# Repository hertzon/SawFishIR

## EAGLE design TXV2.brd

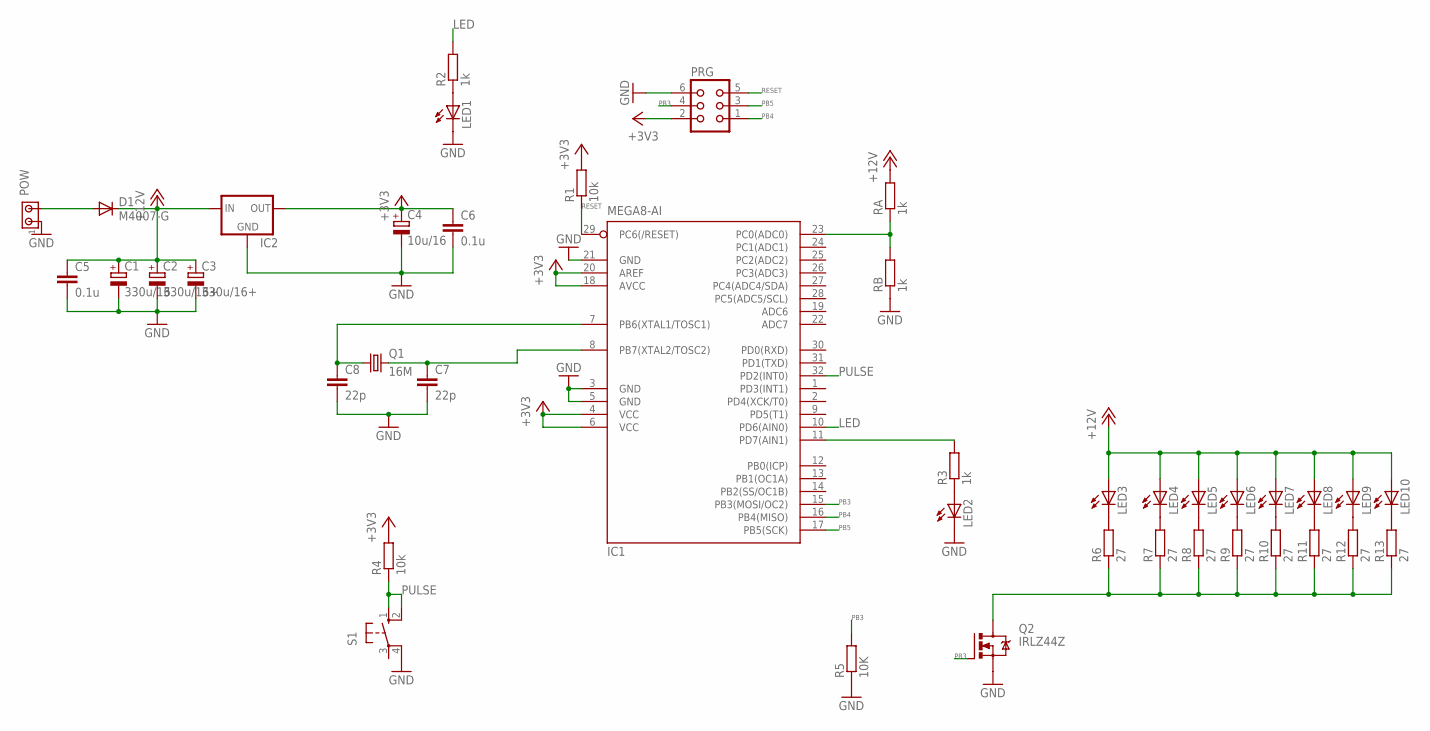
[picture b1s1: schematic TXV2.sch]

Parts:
C1: 330u/16; E2,5-7
C2, C3: 330u/16+; E2,5-7
C4: 10u/16; E2,5-6
C5, C6: 0.1u; C0402
C7, C8: 22p; C0805
D1: M4007-G; SOD-123_MINI-SMA
IC1: MEGA8-AI; TQFP32-08
IC2: 78LXX
LED1, LED2, LED3, LED4, LED5, LED6, LED7, LED8, LED9, LED10: LED5MM
POW: MTA02-100; 10X02MTA
PRG: CON06
Q1: 16M; HC49UP
Q2: IRLZ44Z; TO220BH
R1, R4: 10k; M1206
R2, R3: 1k; M1206
R5: 10K; M1206
R6, R7, R8, R9, R10, R11, R12, R13: 27; 0204/7
RA: 1k; M1206
RB: 1k; M1206
S1: 10-XX; B3F-10XX

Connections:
+3V3: C4.+, C6.1, IC1.4 (VCC), IC1.6 (VCC), IC1.18 (AVCC), IC1.20 (AREF), IC2.OUT, PRG.2, R1.2, R4.2
+12V: C1.+, C2.+, C3.+, C5.1, D1.C, IC2.IN, LED3.A, LED4.A, LED5.A, LED6.A, LED7.A, LED8.A, LED9.A, LED10.A, RA.2
GND: C1.-, C2.-, C3.-, C4.-, C5.2, C6.2, C7.2, C8.2, IC1.3 (GND), IC1.5 (GND), IC1.21 (GND), IC2.GND, LED1.K (C), LED2.K (C), POW.1, PRG.6, Q2.S, R5.1, RB.1, S1.4 (P1)
LED: IC1.10 (PD6(AIN0)), R2.2
unnamed: LED3.K (C), R6.2
unnamed: LED1.A, R2.1
unnamed: IC1.11 (PD7(AIN1)), R3.2
unnamed: LED2.A, R3.1
unnamed: LED4.K (C), R7.2
unnamed: C8.1, IC1.7 (PB6(XTAL1/TOSC1)), Q1.1
unnamed: C7.1, IC1.8 (PB7(XTAL2/TOSC2)), Q1.2
unnamed: LED5.K (C), R8.2
unnamed: LED6.K (C), R9.2
unnamed: LED7.K (C), R10.2
unnamed: LED8.K (C), R11.2
unnamed: LED9.K (C), R12.2
unnamed: LED10.K (C), R13.2
unnamed: IC1.23 (PC0(ADC0)), RA.1, RB.2
unnamed: Q2.D, R6.1, R7.1, R8.1, R9.1, R10.1, R11.1, R12.1, R13.1
unnamed: D1.A, POW.2
PB3: IC1.15 (PB3(MOSI/OC2)), PRG.4, Q2.G, R5.2
PB4: IC1.16 (PB4(MISO)), PRG.1
PB5: IC1.17 (PB5(SCK)), PRG.3
PULSE: IC1.32 (PD2(INT0)), R4.1, S1.1 (S), S1.2 (S1)
RESET: IC1.29 (PC6(/RESET)), PRG.5, R1.1

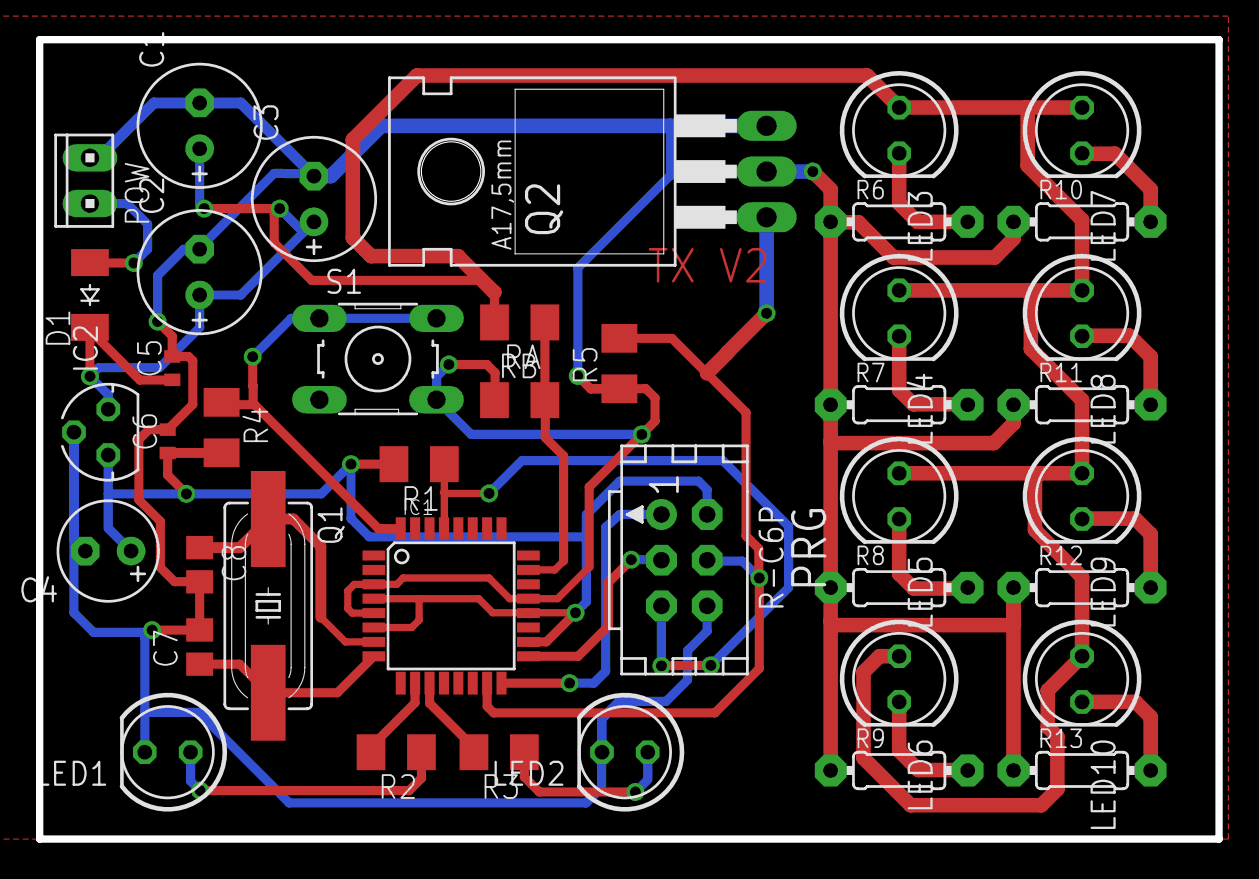
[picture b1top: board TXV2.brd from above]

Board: 2 copper layers, 65.5 x 44.4 mm, 41 parts (0 on the bottom side), 25 nets.

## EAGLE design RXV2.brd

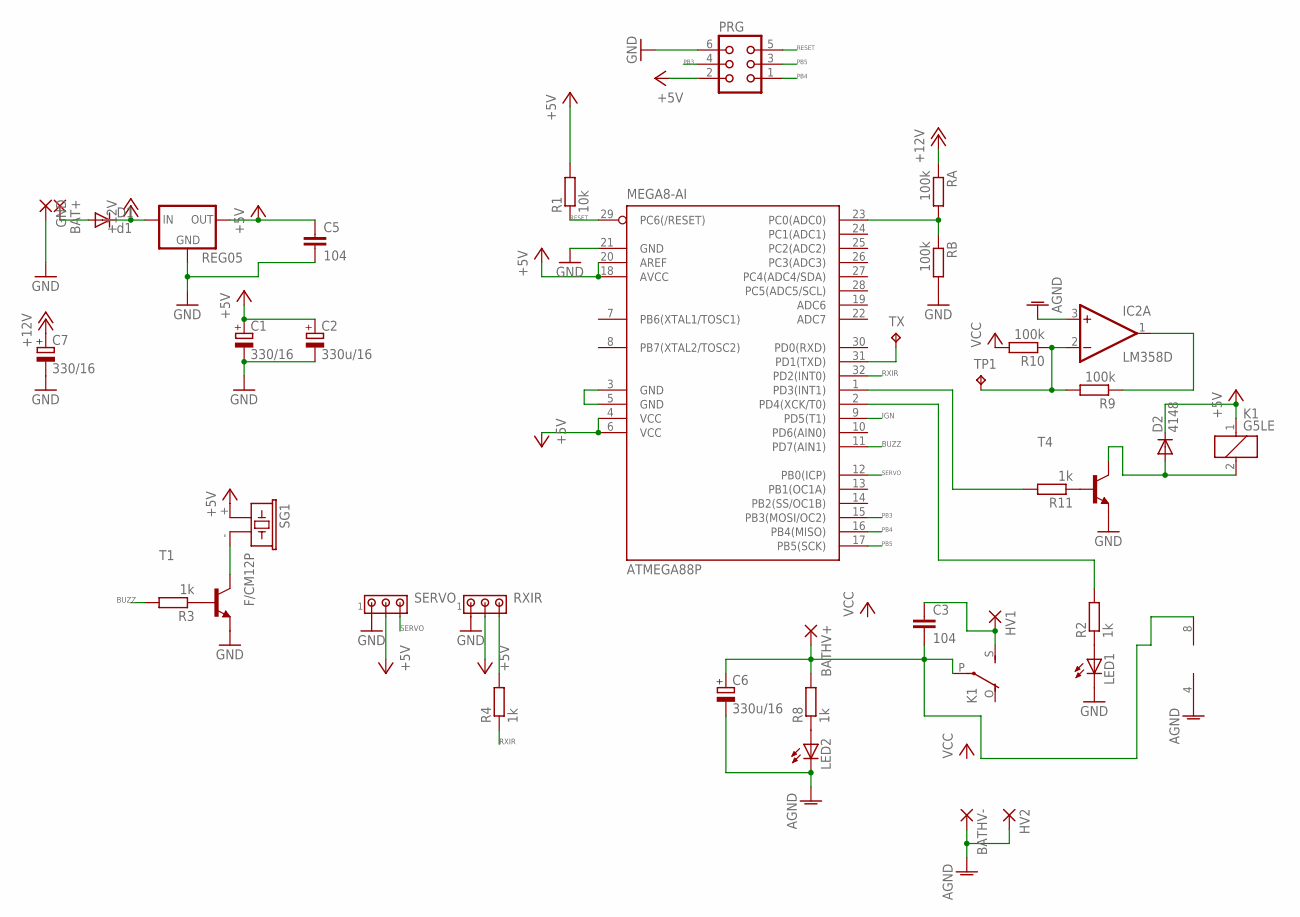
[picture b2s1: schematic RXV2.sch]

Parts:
ATMEGA88P: MEGA8-AI; TQFP32-08
BAT+: SMD5; SMD2,54-5,08
BATHV+: SMD5; SMD2,54-5,08
BATHV-: SMD5; SMD2,54-5,08
C1, C7: 330/16; E2,5-7
C2, C6: 330u/16; E2,5-6
C3: 104; C0805
C5: 104; C2.5-2
D1: d1; SOD-123_MINI-SMA
D2: 4148; DO35-7
GND: SMD5; SMD2,54-5,08
HV1, HV2: SMD5; SMD2,54-5,08
IC2: LM358D; SO08
K1: G5LE
LED1, LED2: LEDCHIPLED_0805; CHIPLED_0805
PRG: CON06
R1: 10k; M1206
R2, R3, R4, R8, R11: 1k; M1206
R9, R10: 100k; M1206
RA: 100k; M1206
RB: 100k; M1206
REG05: 78XXS
RXIR: MTA03-100; 10X03MTA
SERVO: MTA03-100; 10X03MTA
SG1: F/CM12P
T1, T4: MMBT2222ALT1-NPN-SOT23-BEC; SOT23-BEC
TP1: TPTP19R; TP19R
TX: TPTP19R; TP19R

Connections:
+5V: ATMEGA88P.4 (VCC), ATMEGA88P.6 (VCC), ATMEGA88P.18 (AVCC), ATMEGA88P.20 (AREF), C1.+, C2.+, C5.1, D2.C, K1.1, PRG.2, R1.2, REG05.OUT, RXIR.2, SERVO.2, SG1.+ (1)
+12V: C7.+, D1.C, RA.1, REG05.IN
AGND: BATHV-.1, C6.-, HV2.1, IC2.3 (+IN), IC2.4 (V-), LED2.C
BUZZ: ATMEGA88P.11 (PD7(AIN1)), R3.2
GND: ATMEGA88P.21 (GND), C1.-, C2.-, C5.2, C7.-, GND.1, LED1.C, PRG.6, RB.2, REG05.GND, RXIR.1, SERVO.1, T1.E, T4.E
IGN: ATMEGA88P.9 (PD5(T1))
unnamed: ATMEGA88P.3 (GND), ATMEGA88P.5 (GND)
unnamed: BAT+.1, D1.A
unnamed: R11.1, T4.B
unnamed: SG1.- (2), T1.C
unnamed: LED1.A, R2.1
unnamed: R3.1, T1.B
unnamed: R4.2, RXIR.3
unnamed: BATHV+.1, C3.2, C6.+, IC2.8 (V+), K1.P, R8.2
unnamed: ATMEGA88P.31 (PD1(TXD)), TX.TP
unnamed: ATMEGA88P.23 (PC0(ADC0)), RA.2, RB.1
unnamed: ATMEGA88P.2 (PD4(XCK/T0)), R2.2
unnamed: LED2.A, R8.1
unnamed: IC2.2 (-IN), R9.2, R10.1, TP1.TP
unnamed: IC2.1 (OUT), R9.1
unnamed: ATMEGA88P.1 (PD3(INT1)), R11.2
unnamed: C3.1, HV1.1, K1.S
unnamed: D2.A, K1.2, T4.C
PB3: ATMEGA88P.15 (PB3(MOSI/OC2)), PRG.4
PB4: ATMEGA88P.16 (PB4(MISO)), PRG.1
PB5: ATMEGA88P.17 (PB5(SCK)), PRG.3
RESET: ATMEGA88P.29 (PC6(/RESET)), PRG.5, R1.1
RXIR: ATMEGA88P.32 (PD2(INT0)), R4.1
SERVO: ATMEGA88P.12 (PB0(ICP)), SERVO.3
VCC: R10.2

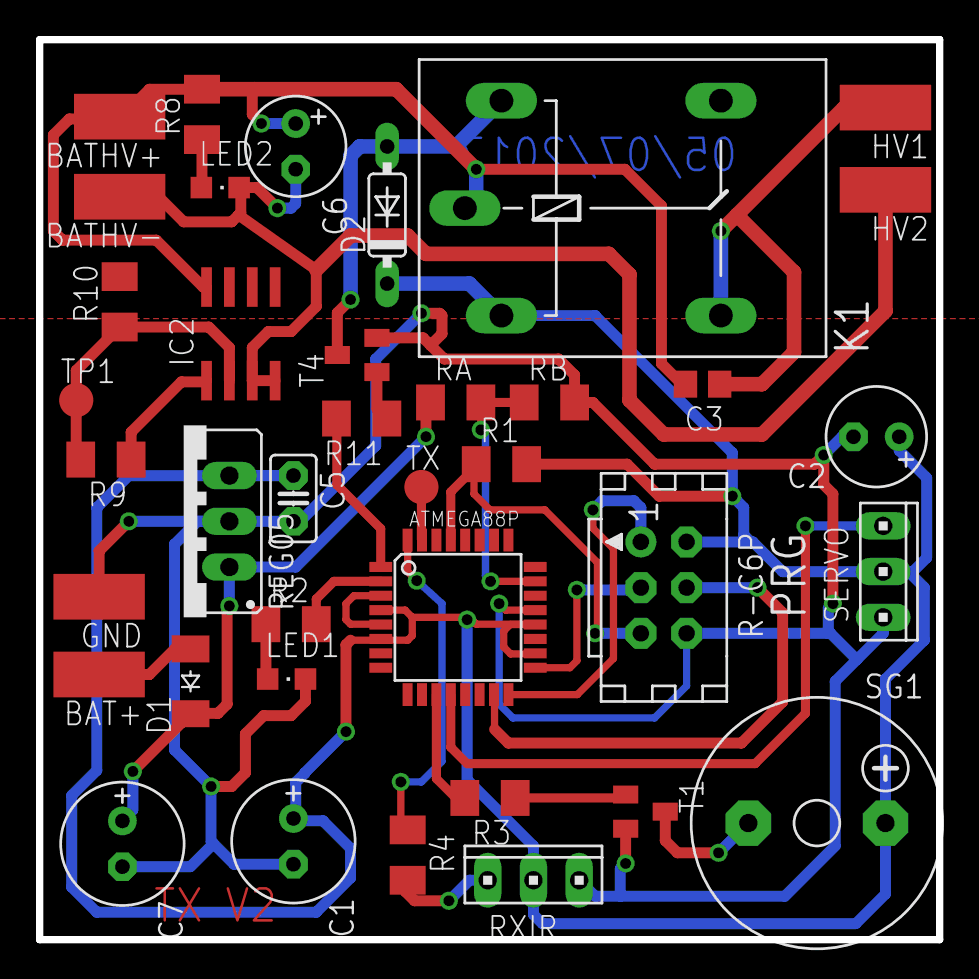
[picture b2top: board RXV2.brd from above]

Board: 2 copper layers, 50.0 x 50.0 mm, 38 parts (0 on the bottom side), 28 nets.

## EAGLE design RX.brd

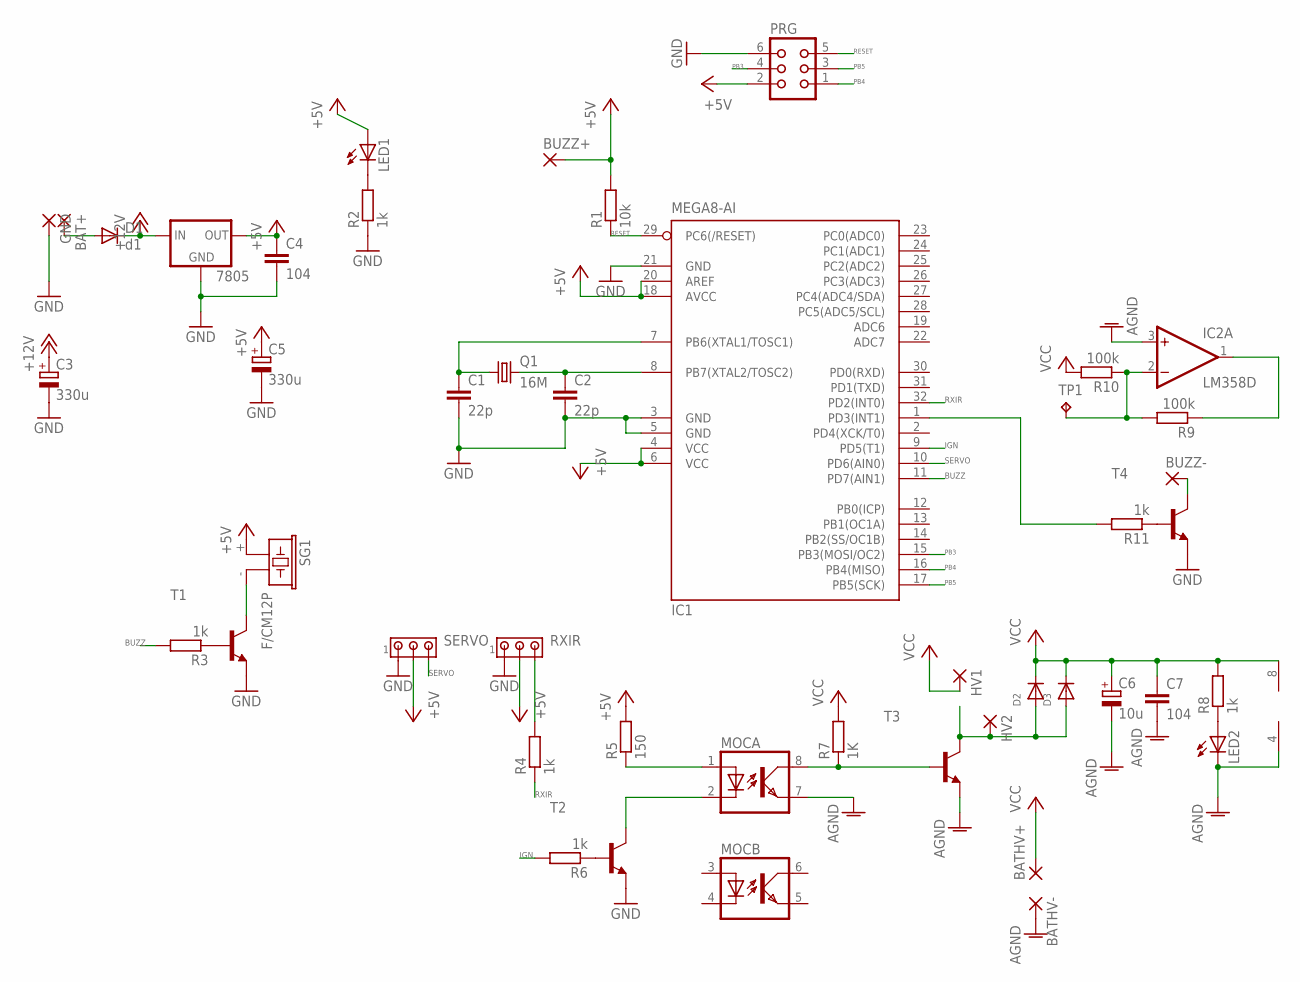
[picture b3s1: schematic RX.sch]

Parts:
7805: 78LXX
BAT+: SMD5; SMD2,54-5,08
BATHV+: SMD5; SMD2,54-5,08
BATHV-: SMD5; SMD2,54-5,08
BUZZ+: SMD2; SMD1,27-2,54
BUZZ-: SMD2; SMD1,27-2,54
C1, C2: 22p; C0805
C3, C5: 330u; 140CLH-1010
C4, C7: 104; C0805
C6: 10u; 140CLH-0810
D1: d1; SOD-123_MINI-SMA
D2, D3: DIODE_SOD-123FL; SOD-123FL
GND: SMD5; SMD2,54-5,08
HV1, HV2: SMD5; SMD2,54-5,08
IC1: MEGA8-AI; TQFP32-08
IC2: LM358D; SO08
LED1: LED3MM
LED2: LEDCHIPLED_0805; CHIPLED_0805
MOC: MOCD207M; SOIC08-FAIRCHILD
PRG: CON06
Q1: 16M; HC49UP
R1: 10k; M1206
R2, R3, R4, R6, R8, R11: 1k; M1206
R5: 150; M1206
R7: 1K; M1206
R9, R10: 100k; M1206
RXIR: MTA03-100; 10X03MTA
SERVO: MTA03-100; 10X03MTA
SG1: F/CM12P
T1, T2, T3, T4: MMBT2222ALT1-NPN-SOT23-BEC; SOT23-BEC
TP1: TPTP10R; TP10R

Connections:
+5V: 7805.OUT, BUZZ+.1, C4.1, C5.+, IC1.4 (VCC), IC1.6 (VCC), IC1.18 (AVCC), IC1.20 (AREF), LED1.A, PRG.2, R1.2, R5.2, RXIR.2, SERVO.2, SG1.+ (1)
+12V: 7805.IN, C3.+, D1.C
AGND: BATHV-.1, C6.-, C7.2, IC2.3 (+IN), IC2.4 (V-), LED2.C, MOC.7 (EMIT), T3.E
BUZZ: IC1.11 (PD7(AIN1)), R3.2
GND: 7805.GND, C1.2, C2.2, C3.-, C4.2, C5.-, GND.1, IC1.3 (GND), IC1.5 (GND), IC1.21 (GND), PRG.6, R2.1, RXIR.1, SERVO.1, T1.E, T2.E, T4.E
IGN: IC1.9 (PD5(T1)), R6.2
unnamed: C2.1, IC1.8 (PB7(XTAL2/TOSC2)), Q1.2
unnamed: C1.1, IC1.7 (PB6(XTAL1/TOSC1)), Q1.1
unnamed: BAT+.1, D1.A
unnamed: R11.1, T4.B
unnamed: SG1.- (2), T1.C
unnamed: LED1.K (C), R2.2
unnamed: R3.1, T1.B
unnamed: R4.2, RXIR.3
unnamed: MOC.2 (C), T2.C
unnamed: MOC.1 (A), R5.1
unnamed: R6.1, T2.B
unnamed: MOC.8 (COL), R7.1, T3.B
unnamed: D2.A, D3.A, HV2.1, T3.C
unnamed: LED2.A, R8.1
unnamed: IC2.2 (-IN), R9.2, R10.1, TP1.TP
unnamed: IC2.1 (OUT), R9.1
unnamed: IC1.1 (PD3(INT1)), R11.2
unnamed: BUZZ-.1, T4.C
PB3: IC1.15 (PB3(MOSI/OC2)), PRG.4
PB4: IC1.16 (PB4(MISO)), PRG.1
PB5: IC1.17 (PB5(SCK)), PRG.3
RESET: IC1.29 (PC6(/RESET)), PRG.5, R1.1
RXIR: IC1.32 (PD2(INT0)), R4.1
SERVO: IC1.10 (PD6(AIN0)), SERVO.3
VCC: BATHV+.1, C6.+, C7.1, D2.C, D3.C, HV1.1, IC2.8 (V+), R7.2, R8.2, R10.2

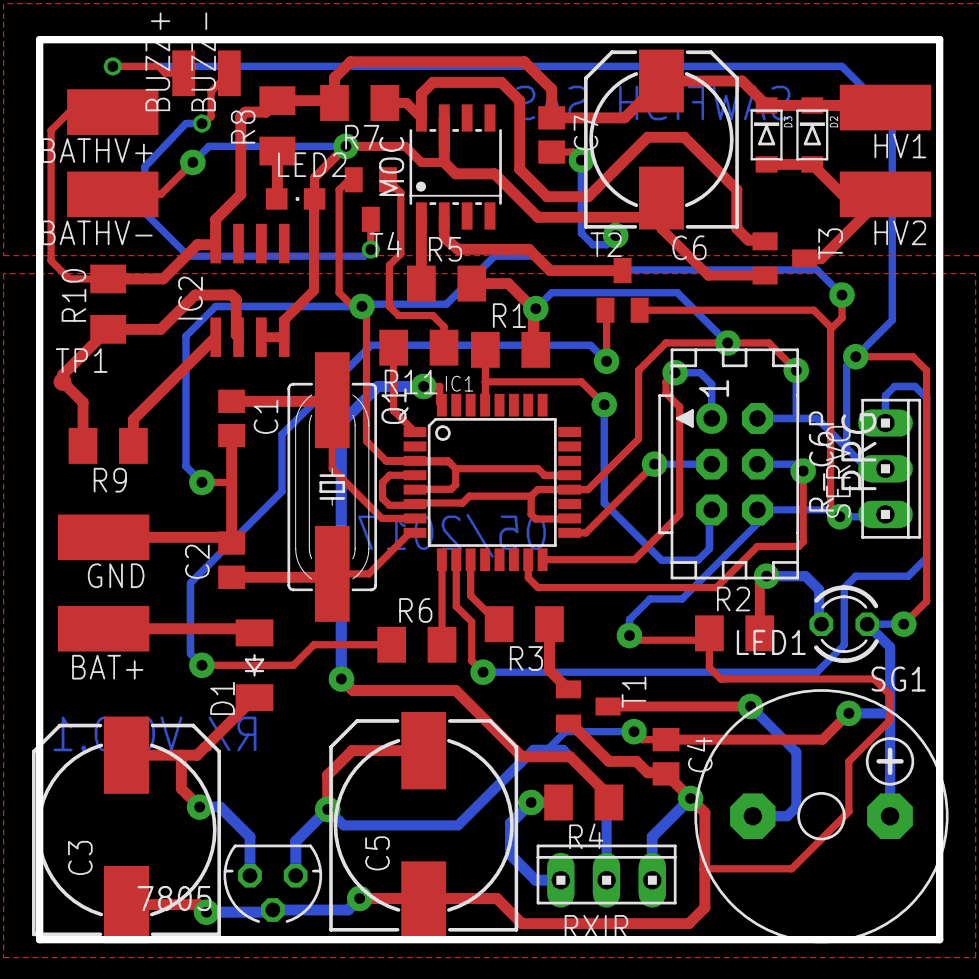
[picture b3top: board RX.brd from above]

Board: 2 copper layers, 50.0 x 50.0 mm, 45 parts (0 on the bottom side), 31 nets.

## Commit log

2017-05-22 first commit 21/05/2071
2017-05-24 23/05/2017
2017-05-29 28/05/2017
2017-06-22 21/06/2017
2017-07-06 05/07/2017
2017-07-22 22/07/2017
2017-07-23 version 2
